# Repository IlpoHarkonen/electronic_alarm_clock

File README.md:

electronic_alarm_clock 2016
Project done by Ville, Pavel and Ilpo

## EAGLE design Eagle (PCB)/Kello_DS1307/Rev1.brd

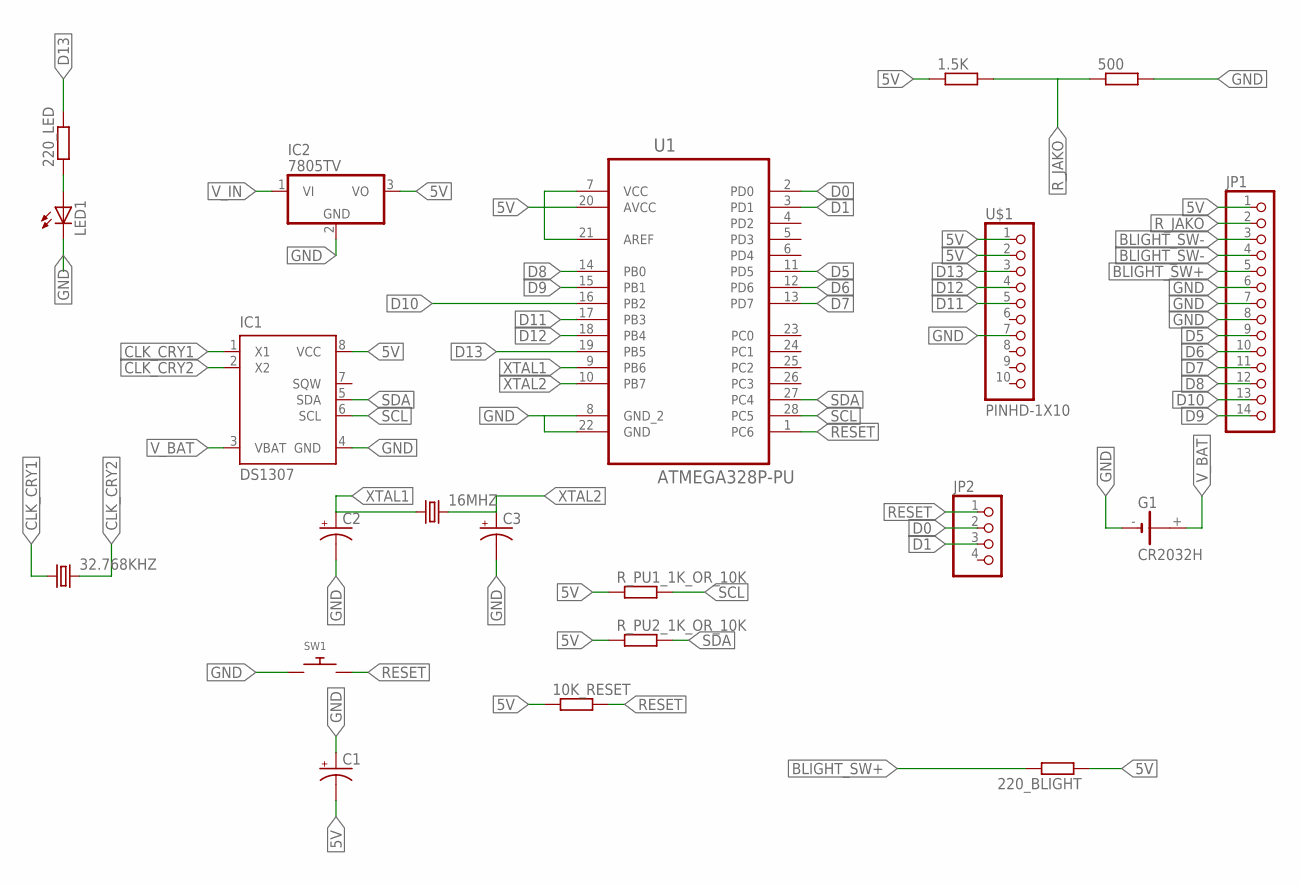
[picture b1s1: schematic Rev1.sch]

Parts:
1.5K, 10K_RESET, 220_BLIGHT, 220_LED, 500: R-EU_0207/10; 0207/10
16MHZ: CRYSTALHC49S; HC49/S
32.768KHZ: CRYSTALTC38H; TC38H
C1, C2, C3: CPOL-USE2,5-6E; E2,5-6E
G1: CR2032H
IC1: DS1307; DIP-8
IC2: 7805TV; TO220V
JP1: PINHD-1X14; 1X14
JP2: PINHD-1X4; 1X04
LED1: LED3MM
R_PU1_1K_OR_10K, R_PU2_1K_OR_10K: R-EU_0207/10; 0207/10
SW1: SWITCH_PUSHBUTTONEVQ-PE; TACT_PANA-EVQ
U1: ATMEGA328P-PU; DIP254P762X457-28
U$1: PINHD-1X10; 1X10-BIG

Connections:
5V: 1.5K.1, 10K_RESET.1, 220_BLIGHT.1, C1.-, IC1.8 (VCC), IC2.3 (VO), JP1.1, R_PU1_1K_OR_10K.1, R_PU2_1K_OR_10K.1, U1.7 (VCC), U1.20 (AVCC), U1.21 (AREF), U$1.1, U$1.2
BLIGHT_SW+: 220_BLIGHT.2, JP1.5
BLIGHT_SW-: JP1.3, JP1.4
CLK_CRY1: 32.768KHZ.1, IC1.1 (X1)
CLK_CRY2: 32.768KHZ.2, IC1.2 (X2)
D0: JP2.2, U1.2 (PD0)
D1: JP2.3, U1.3 (PD1)
D5: JP1.9, U1.11 (PD5)
D6: JP1.10, U1.12 (PD6)
D7: JP1.11, U1.13 (PD7)
D8: JP1.12, U1.14 (PB0)
D9: JP1.14, U1.15 (PB1)
D10: JP1.13, U1.16 (PB2)
D11: U1.17 (PB3), U$1.5
D12: U1.18 (PB4), U$1.4
D13: 220_LED.2, U1.19 (PB5), U$1.3
GND: 500.2, C1.+, C2.-, C3.-, G1.-, IC1.4 (GND), IC2.2 (GND), JP1.6, JP1.7, JP1.8, LED1.K (C), SW1.P$1, U1.8 (GND_2), U1.22 (GND), U$1.7
unnamed: 220_LED.1, LED1.A
RESET: 10K_RESET.2, JP2.1, SW1.P$2, U1.1 (PC6)
R_JAKO: 1.5K.2, 500.1, JP1.2
SCL: IC1.6 (SCL), R_PU1_1K_OR_10K.2, U1.28 (PC5)
SDA: IC1.5 (SDA), R_PU2_1K_OR_10K.2, U1.27 (PC4)
V_BAT: G1.+, IC1.3 (VBAT)
V_IN: IC2.1 (VI)
XTAL1: 16MHZ.1, C2.+, U1.9 (PB6)
XTAL2: 16MHZ.2, C3.+, U1.10 (PB7)

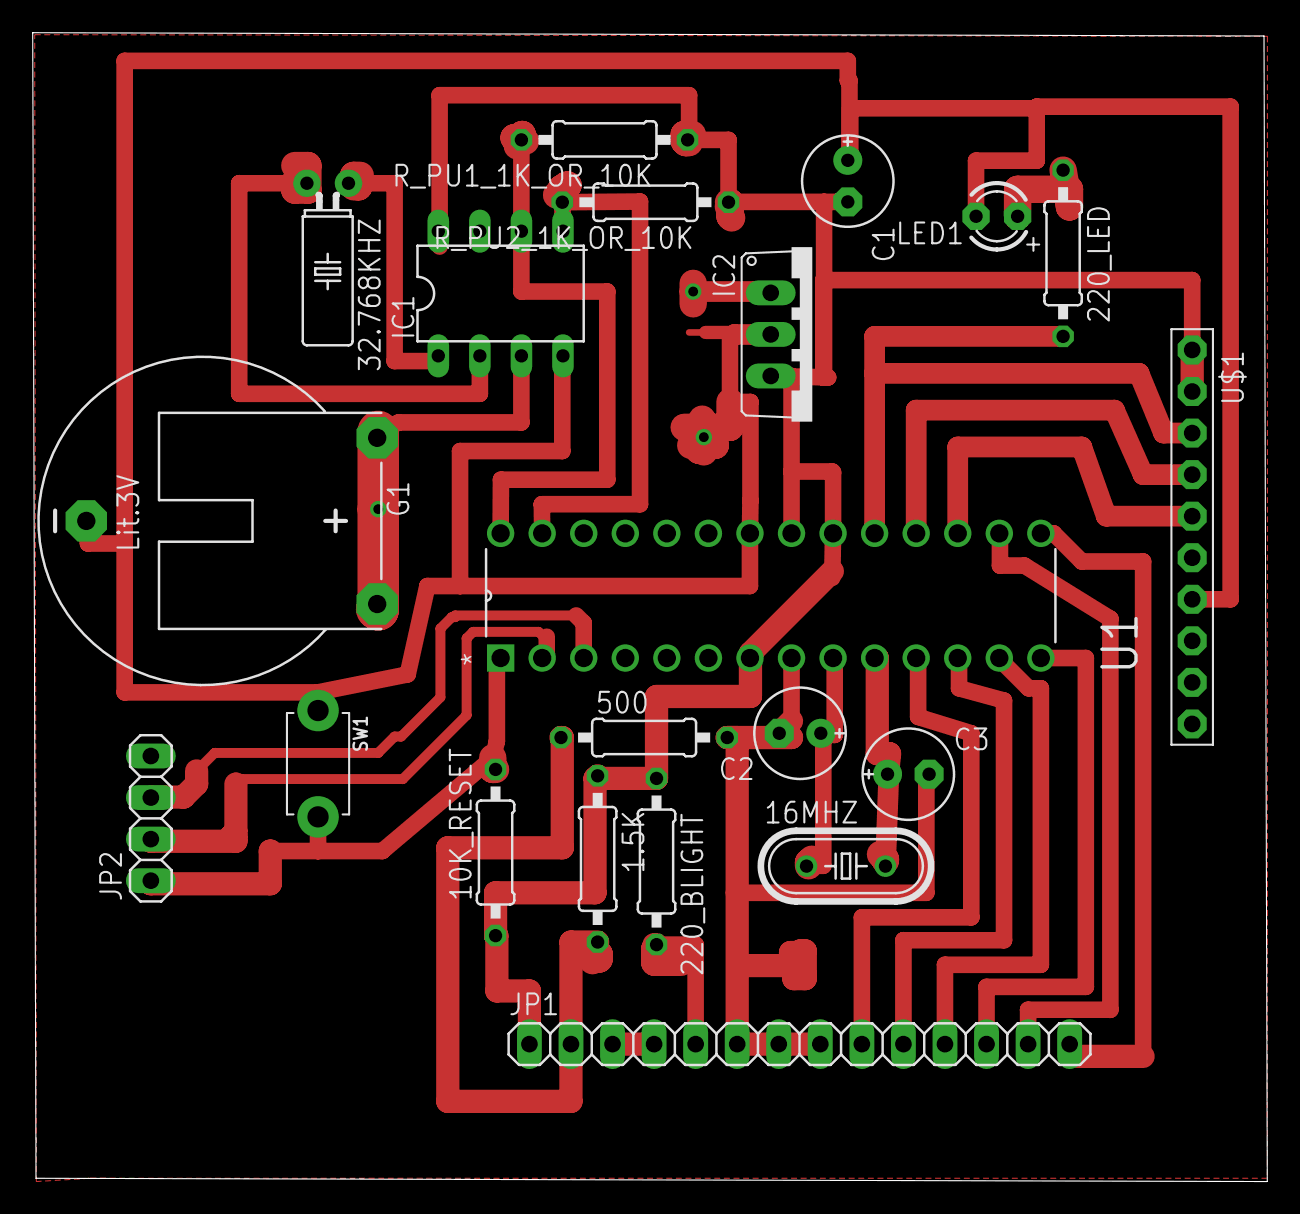
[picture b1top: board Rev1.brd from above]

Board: 2 copper layers, 75.5 x 70.2 mm, 21 parts (0 on the bottom side), 25 nets.

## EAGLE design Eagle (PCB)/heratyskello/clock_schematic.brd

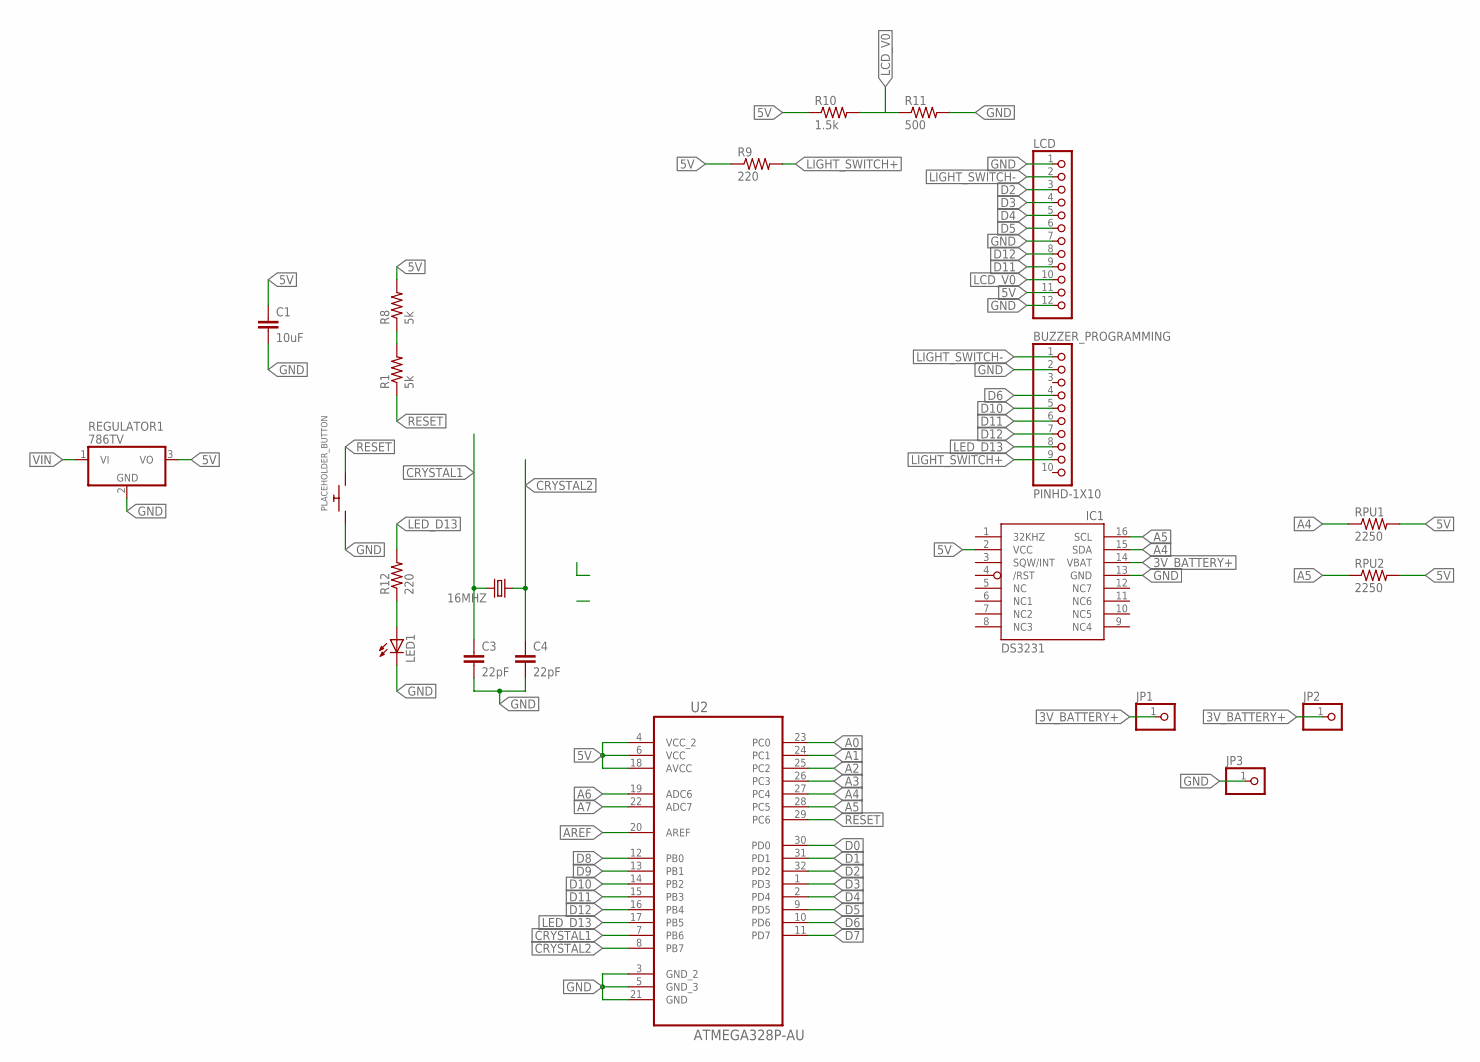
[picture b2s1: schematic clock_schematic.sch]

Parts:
16MHZ: CRYSTALHC18U-V; HC18U-V
BUZZER_PROGRAMMING: PINHD-1X10; 1X10-BIG
C1: 10uF; 0805
C3, C4: 22pF; 0805
IC1: DS3231/SO; SO16W
JP1, JP2, JP3: PINHD-1X1; 1X01
LCD: PINHD-1X12; 1X12
LED1: LEDCHIPLED_0805; CHIPLED_0805
PLACEHOLDER_BUTTON: SWITCH_PUSHBUTTONSOFTTOUCHSMD_SJ; PUSHBUTTON_SMD_SJ
R1, R8: 5k; 0805
R9, R12: 220; 0805
R10: 1.5k; 0805
R11: 500; 0805
REGULATOR1: 786TV; TO220V
RPU1, RPU2: 2250; 0805
U2: ATMEGA328P-AU; QFP80P900X900X120-32N

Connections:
3V_BATTERY+: IC1.14 (VBAT), JP1.1, JP2.1
5V: C1.1, IC1.2 (VCC), LCD.11, R8.2, R9.1, R10.1, REGULATOR1.3 (VO), RPU1.2, RPU2.2, U2.4 (VCC_2), U2.6 (VCC), U2.18 (AVCC)
A0: U2.23 (PC0)
A1: U2.24 (PC1)
A2: U2.25 (PC2)
A3: U2.26 (PC3)
A4: IC1.15 (SDA), RPU1.1, U2.27 (PC4)
A5: IC1.16 (SCL), RPU2.1, U2.28 (PC5)
A6: U2.19 (ADC6)
A7: U2.22 (ADC7)
AREF: U2.20 (AREF)
CRYSTAL1: 16MHZ.2, C3.1, U2.7 (PB6)
CRYSTAL2: 16MHZ.1, C4.1, U2.8 (PB7)
D0: U2.30 (PD0)
D1: U2.31 (PD1)
D2: LCD.3, U2.32 (PD2)
D3: LCD.4, U2.1 (PD3)
D4: LCD.5, U2.2 (PD4)
D5: LCD.6, U2.9 (PD5)
D6: BUZZER_PROGRAMMING.4, U2.10 (PD6)
D7: U2.11 (PD7)
D8: U2.12 (PB0)
D9: U2.13 (PB1)
D10: BUZZER_PROGRAMMING.5, U2.14 (PB2)
D11: BUZZER_PROGRAMMING.6, LCD.9, U2.15 (PB3)
D12: BUZZER_PROGRAMMING.7, LCD.8, U2.16 (PB4)
GND: BUZZER_PROGRAMMING.2, C1.2, C3.2, C4.2, IC1.13 (GND), JP3.1, LCD.1, LCD.7, LCD.12, LED1.C, PLACEHOLDER_BUTTON.P$1, R11.2, REGULATOR1.2 (GND), U2.3 (GND_2), U2.5 (GND_3), U2.21 (GND)
LCD_V0: LCD.10, R10.2, R11.1
LED_D13: BUZZER_PROGRAMMING.8, R12.2, U2.17 (PB5)
LIGHT_SWITCH+: BUZZER_PROGRAMMING.9, R9.2
LIGHT_SWITCH-: BUZZER_PROGRAMMING.1, LCD.2
unnamed: R1.2, R8.1
unnamed: LED1.A, R12.1
RESET: PLACEHOLDER_BUTTON.P$2, R1.1, U2.29 (PC6)
VIN: REGULATOR1.1 (VI)

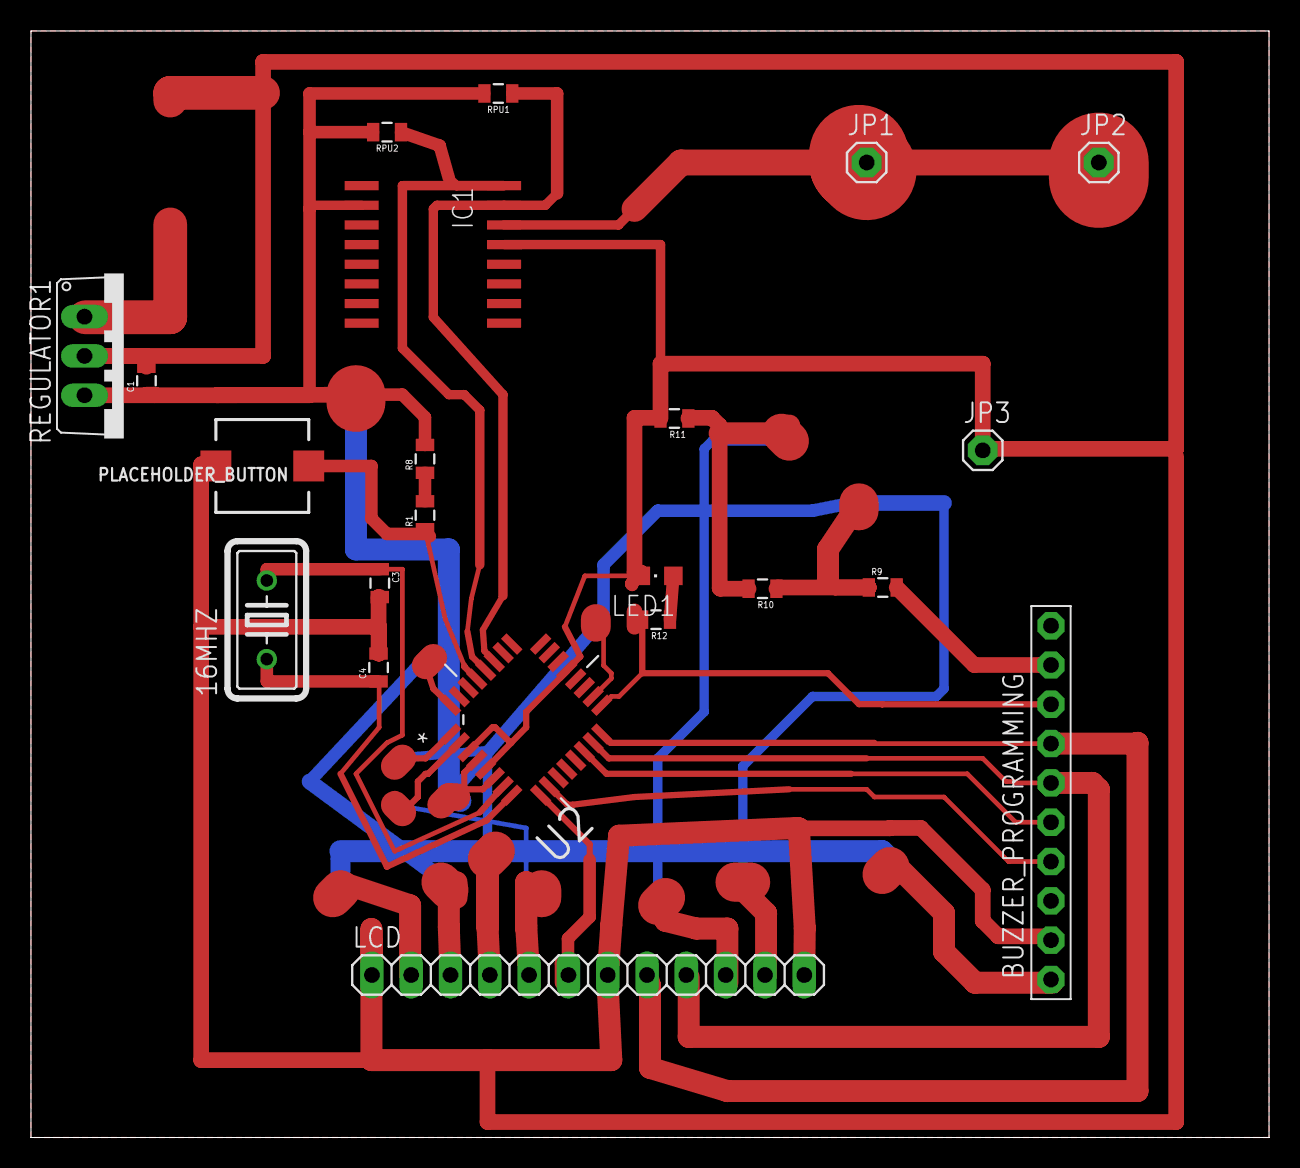
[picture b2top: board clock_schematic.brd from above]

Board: 2 copper layers, 80.0 x 71.5 mm, 22 parts (0 on the bottom side), 22 nets.

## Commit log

2016-09-21 Demo commit
    Ryhmän esittelyä varten
2016-09-22 Demo 2
    Ryhmän live demo
2016-09-29 Volume Symbol Created
    4 character combination from pixels
2016-11-09 Eagle files added
    Placeholder components are marked appropriately. LCD pinheader is not yet confirmed to be in the right physical order. LCD backlight switch and the buzzer can be inserted to the 10-pin pinheader.
2016-11-15 Eagle paths almost made
    Most of the paths are made. Only regulator replacement needed.
2016-11-23 Eagle File Complete
    Regulator was moved to make the PCB smaller. Also moved the 5V connection that was under the 3V battery case lower so it wouldn't be left under the battery.
2016-11-23 Eagle Ground fill done. Ready to print.
2016-11-30 Eagle Fuckup Corrected
    Atmega is now the correct size.
2016-12-01 Arduino Code Added
    RTC Functionality, basic states and some printing functionality implemented. Display_menu_set_time still needs to be refactored.
2016-12-01 Slight refactoring
    Time setting menu refactored a bit. Needs to be broken down to multiple functions.
2016-12-01 Split the code into sub-categories and refactored LCD commands
    Main loop, LCD commands and RTC commands are now located on different files to achieve easier editing. LCD commands were refactored and split into smaller functions to avoid unnecessary code reuse.
2016-12-04 LCD display functions are now complete
    All possible print out functions defined.
2016-12-04 Code 1.0
    All required functionality implemented. As a bonus; the clock returns to the basic state if user does not give input for a specified time.
2016-12-05 Laser Printing Files Added
    #Ville
2016-12-07 DS1307 PCB Eagle Files added
    As the title says
2016-12-08 Cleaned Buzzer code
    Setting a pinmode seemed to be unnecessary.
2016-12-08 Changed the LCD pins in code to match the board
    D12 -> D5
    D11 -> D6
    D5 -> D7
    D4 -> D8
    D3 -> D9
    D2 -> D10
2016-12-09 Converted the code to DS1307
    ...by rewriting time commands
2016-12-09 Final code (Bare Bones)
    Setting alarm or time, the alarm sound and turning it off works now. Things left out: return to basic state after idle time and blinking of hours or minutes depending on which the user is editing.

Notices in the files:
parts and their libraries:
SparkFun-Resistors: Licensing: Creative Commons ShareAlike 4.0 International - https://creativecommons.org/licenses/by-sa/4.0
